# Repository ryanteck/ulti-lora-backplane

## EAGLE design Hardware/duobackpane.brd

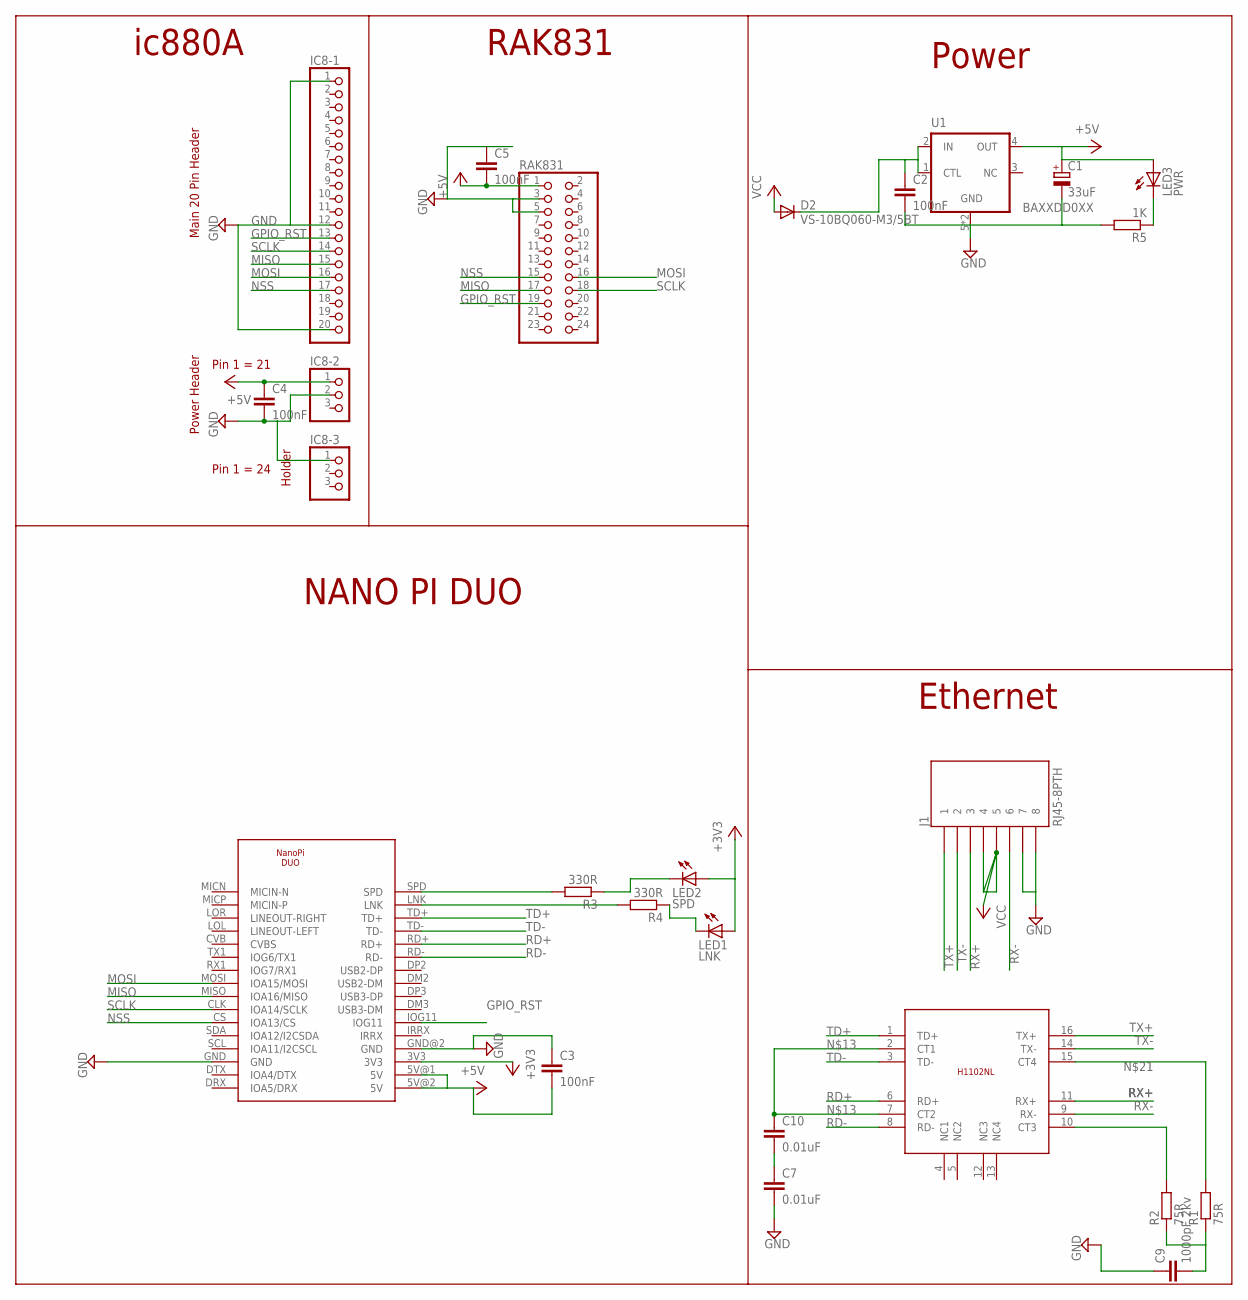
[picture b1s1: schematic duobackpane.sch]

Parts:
C1: 33uF; SMC_A
C2, C3, C4, C5: 100nF; C0805
C7, C10: 0.01uF; C0805
C9: 1000pF 2kv; C1206
D2: VS-10BQ060-M3/5BT; DO214AA
IC8-1: PINHD-1X20; 1X20
IC8-2, IC8-3: PINHD-1X3; 1X03
J1: RJ45-8PTH; RJ45-8
LED1: LNK; SML1206
LED2: SPD; SML1206
LED3: PWR; SML1206
R1, R2: 75R; R0805
R3, R4: 330R; R0805
R5: 1K; R0805
RAK831: PINHD-2X12; 2X12
U1: BAXXDD0XX; HRP5
U$1: DECADE-H1102NL
U$2: NANOPIDUO

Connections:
+3V3: LED1.A, LED2.A, U$2.3V3
+5V: C1.+, C3.2, C4.1, C5.2, IC8-2.1, LED3.A, RAK831.1, U1.4 (OUT), U$2.5V@1 (5V), U$2.5V@2 (5V)
GND: C1.-, C2.2, C3.1, C4.2, C5.1, C7.2, C9.1, IC8-1.1, IC8-1.12, IC8-1.20, IC8-2.2, IC8-3.1, J1.7, J1.8, R5.2, RAK831.3, RAK831.5, U1.5 (GND), U1.6 (GND), U$2.GND, U$2.GND@2 (GND)
GPIO_RST: IC8-1.13, RAK831.19, U$2.IOG11
MISO: IC8-1.15, RAK831.17, U$2.MISO (IOA16/MISO)
MOSI: IC8-1.16, RAK831.16, U$2.MOSI (IOA15/MOSI)
unnamed: C2.1, D2.C, U1.1 (CTL), U1.2 (IN)
unnamed: R3.2, U$2.SPD
unnamed: R4.2, U$2.LNK
unnamed: LED2.C, R3.1
unnamed: R2.2, U$1.10 (CT3)
unnamed: C9.2, R1.1, R2.1
unnamed: LED1.C, R4.1
unnamed: C7.1, C10.2
unnamed: LED3.C, R5.1
unnamed: C10.1, U$1.2 (CT1), U$1.7 (CT2)
unnamed: R1.2, U$1.15 (CT4)
NSS: IC8-1.17, RAK831.15, U$2.CS (IOA13/CS)
RD+: U$1.6 (RD+), U$2.RD+
RD-: U$1.8 (RD-), U$2.RD-
RX+: J1.3, U$1.11 (RX+)
RX-: J1.6, U$1.9 (RX-)
SCLK: IC8-1.14, RAK831.18, U$2.CLK (IOA14/SCLK)
TD+: U$1.1 (TD+), U$2.TD+
TD-: U$1.3 (TD-), U$2.TD-
TX+: J1.1, U$1.16 (TX+)
TX-: J1.2, U$1.14 (TX-)
VCC: D2.A, J1.4, J1.5

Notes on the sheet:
ic880A
RAK831
NANO PI DUO
Power
Ethernet
Main 20 Pin Header
Power Header
Holder
Pin 1 = 21
Pin 1 = 24

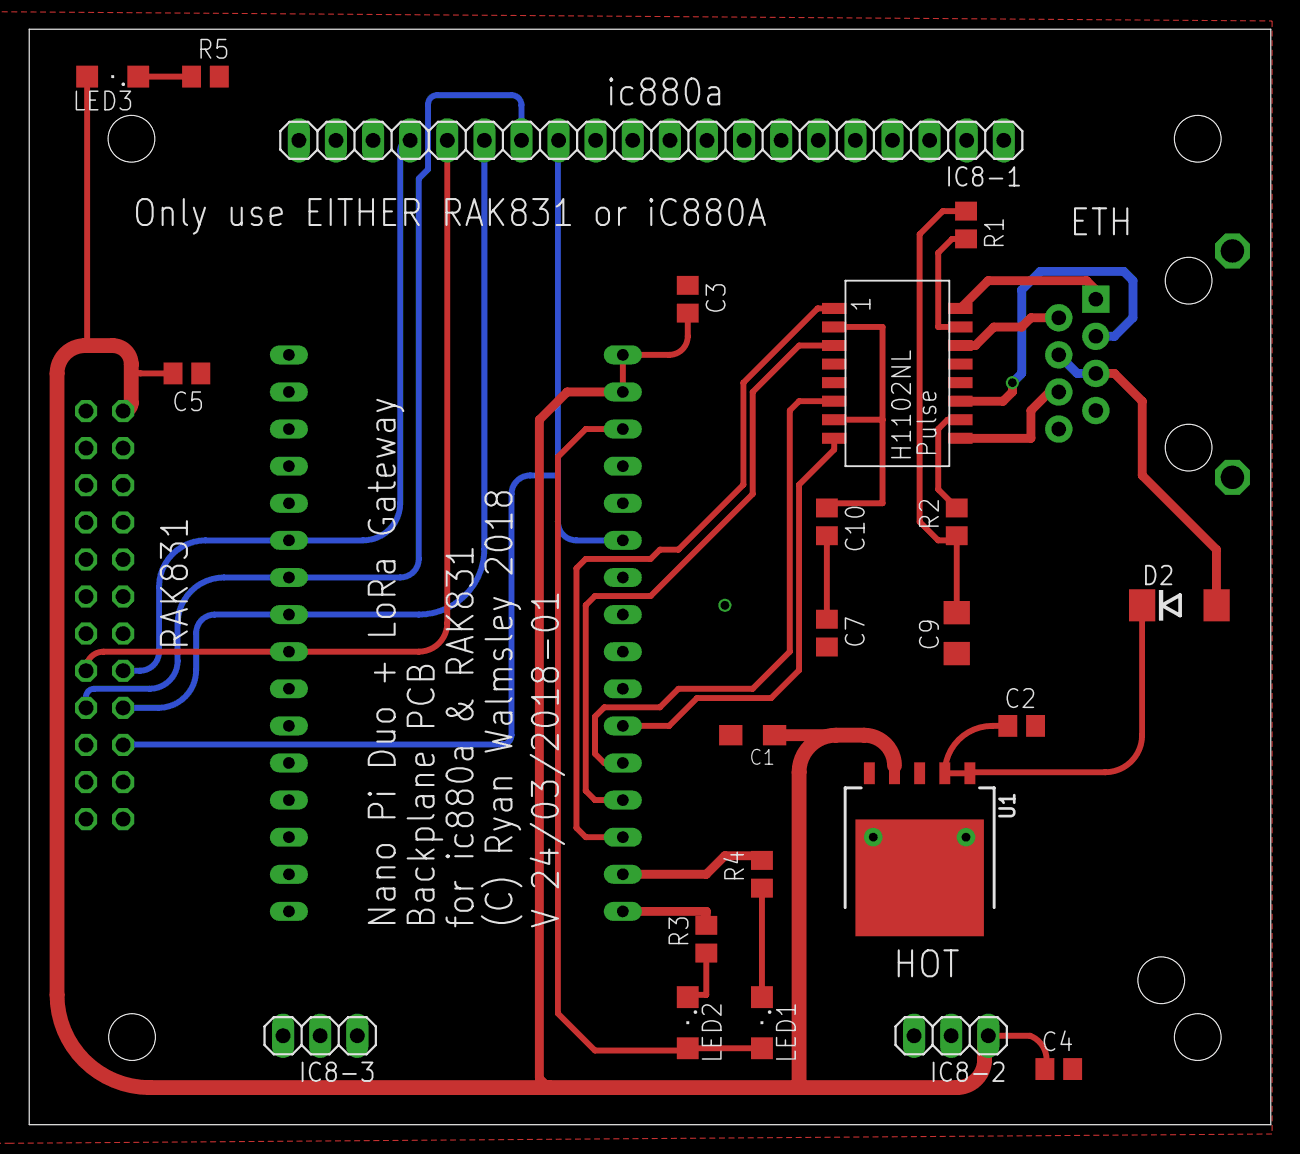
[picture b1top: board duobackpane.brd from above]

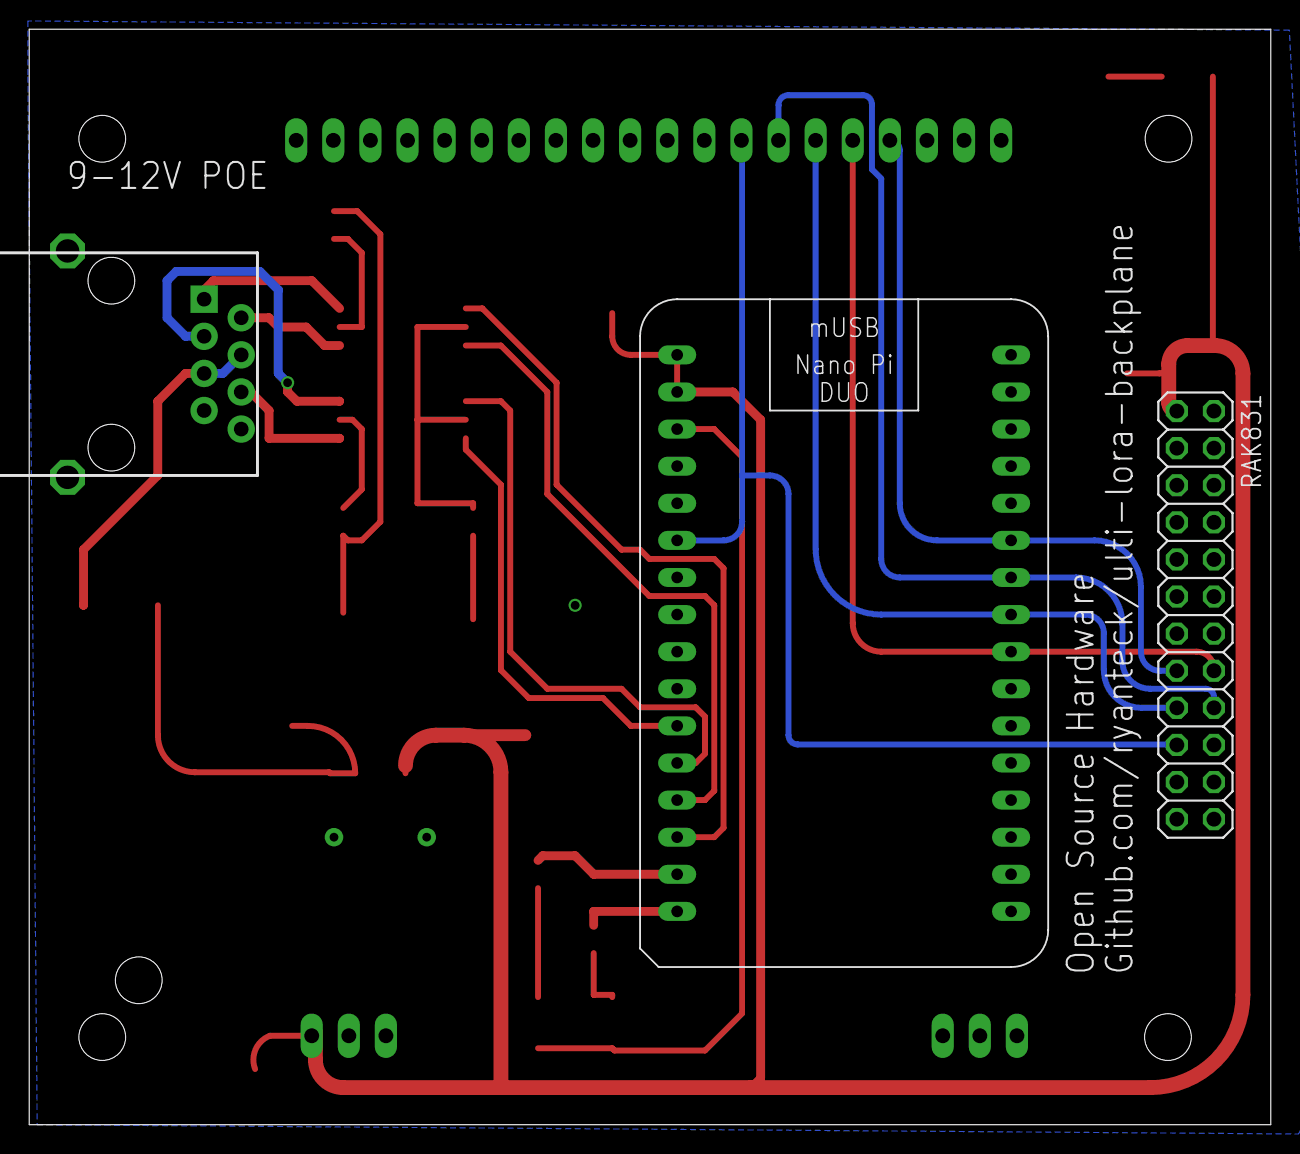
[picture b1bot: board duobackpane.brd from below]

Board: 2 copper layers, 85.0 x 75.0 mm, 25 parts (3 on the bottom side), 28 nets.

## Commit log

2018-03-23 hw
    Added hardware
2018-03-24 Fixed a few bits,
    Commit
2018-03-25 Started attempt at packaging software in a snap
2018-03-25 Porgress made
2018-03-26 So far: Lib lora gw seems to compile fine paho compiles fine ttn connector compiles fine
    packet forwarder is not able to reference the others
2018-03-26 Changed from using the new packet forwarder to the classic one for now
2018-03-29 Changed to Daemon
2018-03-29 Added first attempt at package
2018-04-01 Current working code
2018-04-01 Added 0.1.9
2018-04-02 Started work on changing for multip forwarder
2018-04-02 Moved
2018-04-03 Lotsof progress made, need to compile on arm device
2018-04-03 Slight mod
2018-04-03 Change
2018-04-03 Tried changing libs a little
2018-04-03 rm drpi
2018-04-03 Finally got to install part, i think
2018-04-03 Fixed indent
2018-04-03 Changed command name
2018-04-03 Fixed issue directing to dir instead of file
2018-04-03 Added latest verion
2018-04-03 changed to classic
2018-04-03 changed version no
2018-04-03 Attempt to fix lib issue
2018-04-04 Bump ver
2018-04-04 Bump version
2018-04-04 Changed version, should now include config
2018-04-04 Re-added summary
2018-04-04 New version with spi debug
2018-04-04 Remove spi debug
2018-04-04 Smallened down
2018-04-04 Fixed
2018-04-04 Added debug
2018-04-04 Latest
2018-04-12 Lots of changes
2018-04-13 Changed from classic to devmode
2018-04-15 Re-added multi file
2018-04-21 Archived the snapcraft parts
2018-04-21 Added starter script

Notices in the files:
parts and their libraries:
DECADE-libraries20151104: Licensing: Creative Commons ShareAlike 4.0 International - https://creativecommons.org/licenses/by-sa/4.0
rohm-semi: Copyright (C) 2010, Bob Starr
